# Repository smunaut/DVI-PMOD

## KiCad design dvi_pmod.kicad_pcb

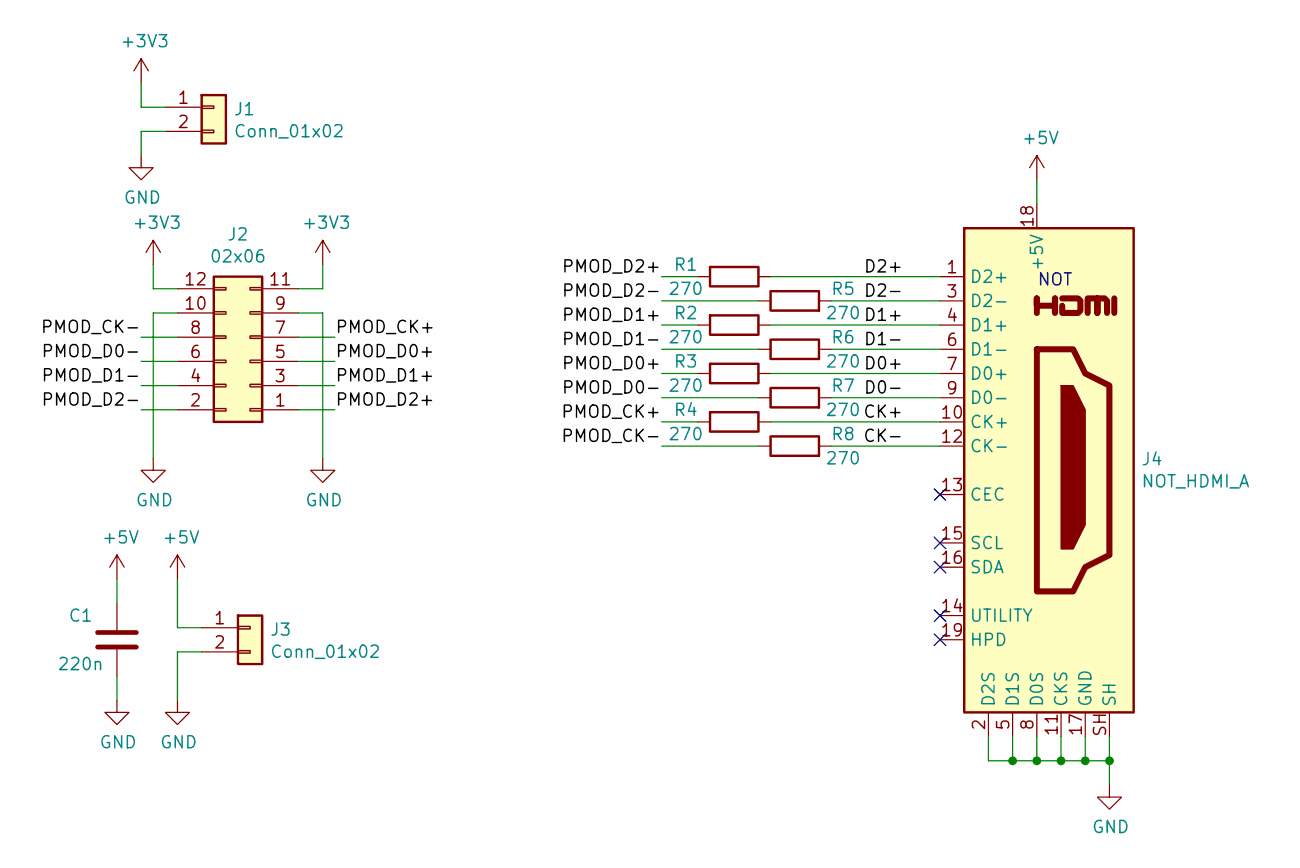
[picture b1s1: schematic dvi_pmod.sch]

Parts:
C1: 220n; C_0402_1005Metric
J1, J3: Conn_01x02; PinHeader_1x02_P2.54mm_Vertical
J2: 02x06; PinSocket_2x06_P2.54mm_Horizontal
J4: NOT_HDMI_A; HDMI-SS-53000
R1, R2, R3, R4, R5, R6, R7, R8: 270; R_0402_1005Metric

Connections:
+3V3: J1.1, J2.11, J2.12
+5V: C1.2, J3.1, J4.18 (+5V)
/CK+: J4.10 (CK+), R4.1
/CK-: J4.12 (CK-), R8.2
/D0+: J4.7 (D0+), R3.1
/D0-: J4.9 (D0-), R7.2
/D1+: J4.4 (D1+), R2.1
/D1-: J4.6 (D1-), R6.2
/D2+: J4.1 (D2+), R1.1
/D2-: J4.3 (D2-), R5.2
/PMOD_CK+: J2.7, R4.2
/PMOD_CK-: J2.8, R8.1
/PMOD_D0+: J2.5, R3.2
/PMOD_D0-: J2.6, R7.1
/PMOD_D1+: J2.3, R2.2
/PMOD_D1-: J2.4, R6.1
/PMOD_D2+: J2.1, R1.2
/PMOD_D2-: J2.2, R5.1
GND: C1.1, J1.2, J2.9, J2.10, J3.2, J4.2 (D2S), J4.5 (D1S), J4.8 (D0S), J4.11 (CKS), J4.17 (GND), J4.SH

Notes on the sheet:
NOT

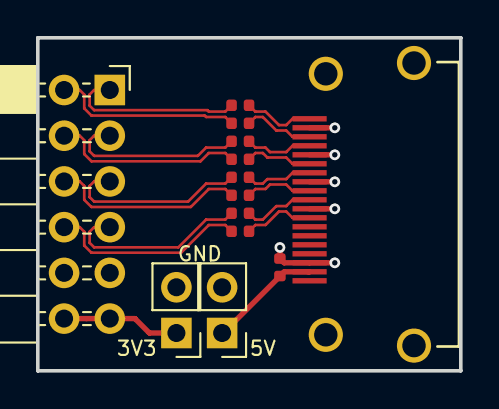
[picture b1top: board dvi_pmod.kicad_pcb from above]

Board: 2 copper layers, 23.5 x 18.5 mm, 13 parts (0 on the bottom side), 19 nets.

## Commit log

2020-11-01 Remove 'bak' files from repo
2020-11-01 New pinout and new layout
2020-11-01 Remove outdated pdf
